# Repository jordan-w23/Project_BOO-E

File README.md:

# Project_BOO-E
This is my Industrial designs project 3 for my 3rd year of Electrical Engineering studies. It is a proof of concept for a low cost autonomous vehicle using open-source recourses.
The system is broken down into 3 subsystems: Power, Navigation, Data logging
Ardupilot online forum is a key tool to use when setting up the flight controller and ground control station as most issues can be solved with a bit of research.

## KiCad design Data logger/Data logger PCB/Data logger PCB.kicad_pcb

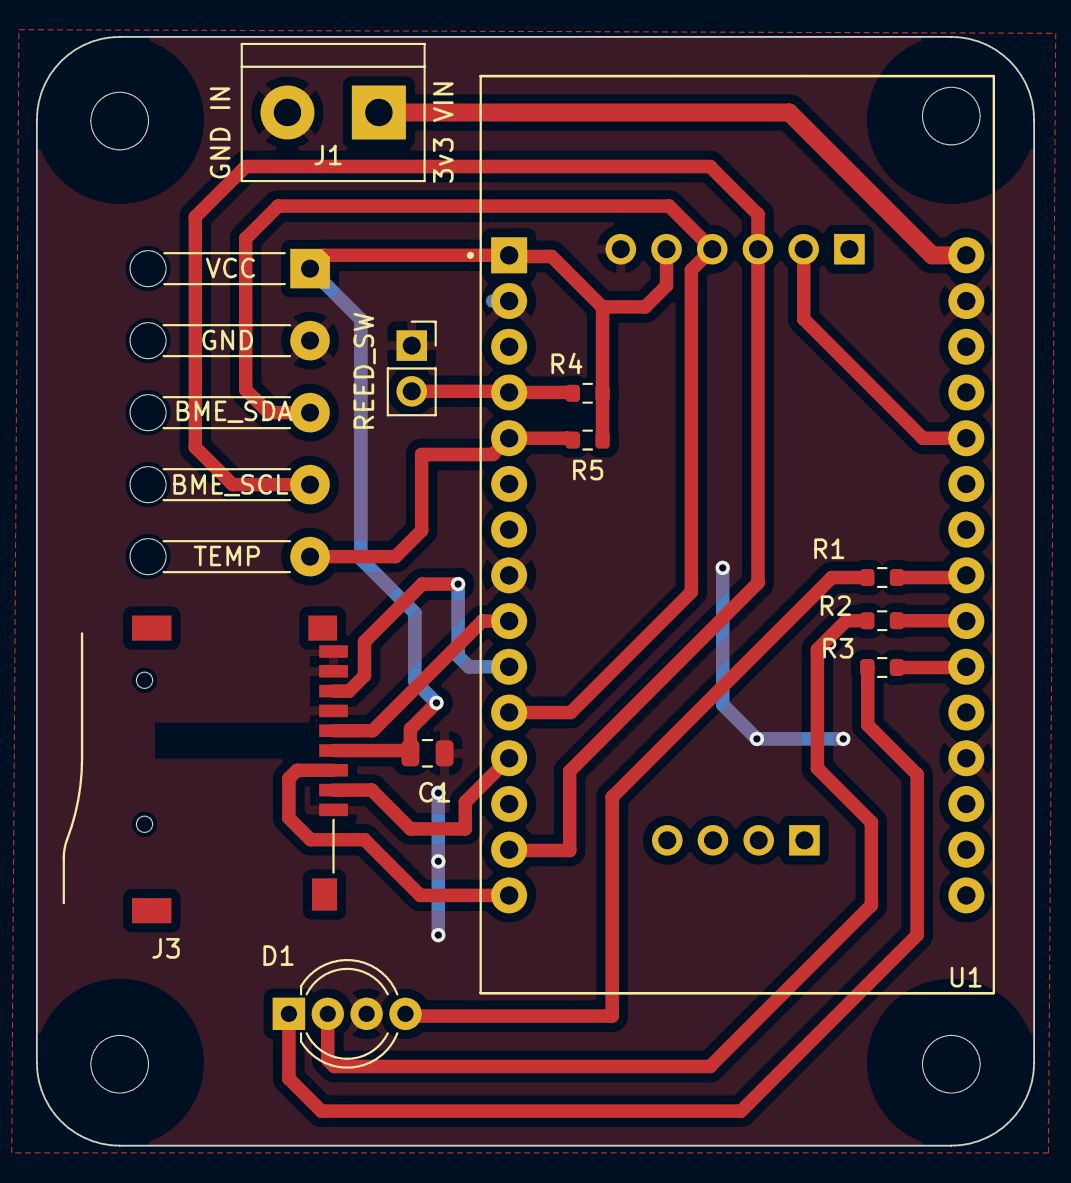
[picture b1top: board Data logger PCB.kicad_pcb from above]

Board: 2 copper layers, 55.4 x 61.6 mm, 13 parts (1 on the bottom side), 18 nets.

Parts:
C1: 100nF; C_0805_2012Metric
D1: LED_RGAB; LED_D5.0mm-4_RGB_Wide_Pins
J1: Conn_01x02; TerminalBlock_bornier-2_P5.08mm
J2: Conn_2Rows-05Pins; SolderWire-0.15sqmm_1x05_P4mm_D0.5mm_OD1.5mm_Relief
J3: Micro_SD_Card; SUNTECH_ST-TF-003A
J5 (RTC): Conn_01x06_Socket; PinHeader_1x06_P2.54mm_Vertical
R1, R2, R3: 220; R_0603_1608Metric
R4: 10k; R_0603_1608Metric
R5: 4k7; R_0603_1608Metric
REED_SW: SW_Reed; PinSocket_1x02_P2.54mm_Vertical
U1: ESP32-DEVKIT-V1; MODULE_ESP32_DEVKIT_V1

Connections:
3v3 VIN: J1.1, U1.30 (VIN)
CLK: J3.5 (CLK), U1.9 (D18)
CS: J3.2 (DAT3/CD), U1.12 (RX0)
GND: C1.2, D1.3 (A), J1.2, J2.2, J3.1 (DAT2), J3.6 (VSS), J3.8 (DAT1), J3.9 (SHIELD), J5 (RTC).6, REED_SW.1, U1.2 (GND), U1.8 (D5), U1.19 (D34), U1.29 (GND)
Idle_status: R1.1, U1.23 (D25)
Log_status: R2.1, U1.22 (D33)
MISO: J3.7 (DAT0), U1.10 (D19)
MOSI: J3.3 (CMD), U1.15 (D23)
unnamed: D1.4 (BK), R1.2
unnamed: D1.2 (GK), R2.2
unnamed: D1.1 (RK), R3.2
REED_SW: R4.1, REED_SW.2, U1.4 (D2)
SCL: J2.4, J5 (RTC).3, U1.14 (D22)
SDA: J2.3, J5 (RTC).4, U1.11 (D21)
SQW*: J5 (RTC).2, U1.26 (D14)
TEMP: J2.5, R5.1, U1.5 (D4)
VCC: C1.1, J2.1, J3.4 (VDD), J5 (RTC).5, R4.2, R5.2, U1.1 (3V3)
Web_status: R3.1, U1.21 (D32)
